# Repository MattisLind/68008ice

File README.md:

# RP2350 MC68008 Emulator and Bus Analyzer

A compact diagnostic adapter for computers using the **48-pin MC68008**. An
RP2350B or RP2354B microcontroller will use PIO, DMA and native USB to observe
the processor bus, generate diagnostic bus cycles and eventually emulate the
CPU in software.

The project now has a [draft pin map, candidate BOM and single-A3 KiCad schematic](kicad/README.md),
using RP2354B with in-package flash and **8 MiB QSPI PSRAM**, plus an
[unrouted four-layer placement starter](docs/mechanical.md). It uses provisional
outward-bent DIP contact lands and an accessible end tab. Firmware bring-up
now includes a [Docker Pico SDK build and verified SWD debugger workflow](docs/bringup.md)
for the standalone Waveshare Core2350B: GPIO39 blink, USB logging, flash read-back,
breakpoints, stepping and halt/resume. Two Core2350B boards have also been
verified with concurrent, independent debugger sessions through one probe on
a shared multidrop SWD connection. A GPIO0 link through the user's 470 ohm
resistor was verified with opposite LED states. The current
[GPIO0–44 connectivity test](docs/gpio-connectivity.md) scans both directions
with LOW and HIGH patterns through SWD. **All 45 paths pass in both directions**
after the user reflowed GPIO6's solder joints on 2026-11-16. The earlier expanded
scans detected that missing path; the earlier GPIO0–38 test found GPIO2's solder
fault before repair. No missing paths, cross-wiring or bridges are detected in
the latest scan. A [PIO bench analyzer and pattern generator](docs/pio-trace.md)
now capture GPIO0–31 and GPIO32–44 in separate 1024-sample runs at a nominal
150 MS/s. Both banks matched the one-bit-per-clock pattern with no receiver
FIFO stalls. The receiver stores `LOW32.VCD` and `HIGH13.VCD` in flash and
exports a read-only USB drive after acquisition; both files survived an SWD reset.
The current [core 0 dispatcher](docs/dispatcher.md) loads generator/analyzer
modules from flash or PSRAM into core 1 execution SRAM. A framed USB CDC
protocol and Python CLI start both applications without SWD. The analyzer
supports HIGH/LOW level triggers on any GPIO0–44 for either bank in its original
finite burst mode.
The dispatcher now exposes only USB CDC; the `ICECAP` mass-storage interface
has been removed. Captures remain in flash and download through CDC.
Dispatcher 0.3 adds an [8 MHz-timed 68008 bench bus generator, a 1 KiB memory
responder and state analyzer](docs/bus-fixture.md). Continuous timing and state
captures support 1..65536 records, address or GPIO triggers, early/middle/late
positions, partial stops and host VCD export. Continuous timing currently accepts
1 kHz..1 MHz; the original finite 150 MS/s path remains available. These are
3.3 V fixture applications with GPIO31 as DTACK, separate from the proposed
motherboard adapter. Dispatcher 0.4 adds a [combined memory/150 MS/s timing
mode](docs/single-cycle-timing.md) for a 4096-sample single-cycle trace with
an exact sampled-edge midpoint trigger. The 100 ms no-trigger capture/timeout
path and single read/write captures are bench verified on both boards, with
zero sampling stalls. The responder currently adds one or two wait states;
the nominal 500 ns no-wait cycle remains a sequencing target. Adapter bus
firmware remains unimplemented. Dispatcher 0.5 adds a
[CPU reset/STOP application](docs/cpu-emulator.md) using the shared PIO byte
bus engine and a boot image in the other board's memory/state analyzer. Both
boards passed reset-vector fetches and `STOP #$2700` (12 captured byte reads),
NOP/STOP (14 reads), and a separate reset-vector BERR-to-HALT test. This is a
reset/NOP/STOP milestone. Dispatcher 0.6 now runs the first five instructions
of the [supplied ABC1600 ROM](docs/abc1600.md), uploaded through the memory
tool into a separate 1 MiB target map. Both cause-register branch paths match
the captured bus bytes and per-instruction register snapshots. CLR,
MOVE/MOVEA, BTST, BRA/BSR/Bcc and JMP passed 37586 independent Musashi
comparisons in host RAM, including the legal MOVE addressing-mode cross-product.
Dispatcher 0.7 now separates generic uploaded-code memory from an ABC1600
memory application with boot-ROM mirrors, task/segment/page registers, MMU
translation and protection. The ROM executes **105 instructions** (the first
five plus the next 100), including 54 MAC writes; all 354 bus transfers, 106
CPU snapshots and MAC tables match the host/MAME reference. The expanded
CPU core passes 81238 independent instruction cases, and the MAC model passes
17133 comparisons against methods extracted from the local MAME checkout.
The extended interpreter now boots the ROM to its **keyboard input wait**
(host: 552468 instructions). A two-board run of 600000 instructions matched
all final registers and 4096 captured bus transfers, with zero bus errors.
See [keyboard boot validation](docs/validation/abc1600-keyboard-2026-11-17/README.md).
The instruction matrix passes 87274 Musashi comparisons. Functional CIO,
DART, SCC, CRTC, VRAM and mover support covers this boot path; complete
peripherals, exception processing, interrupts, remaining opcodes and
CPU-speed validation remain future work. The
[RP2350 engineering specification](requirements/RP2350_68008_ICE_Specification_and_Codex_Prompt.md)
is the design baseline and contains the detailed requirements, acceptance
criteria and primary references.

## Operating modes

| Mode | Physical CPU | Intended behavior |
| --- | --- | --- |
| Passive analyzer | Installed in the upper socket | CPU pins connect directly to the motherboard; the MCU observes with all bus outputs disabled. Capture bounded traces with triggers, timestamps and overflow reporting. |
| CPU replacement | Removed | The MCU drives the motherboard bus. Begin with byte reads/writes and memory diagnostics, then add a software MC68008 interpreter and execution controls. |

Passive mode is the default. A hardware interlock must prevent accidental MCU
bus driving with a real processor installed. Full CPU emulation and original
CPU-speed performance remain development goals requiring validation.

## Hardware concept

- Aligned female contacts on top and male contacts underneath: 48-pin DIP,
  2.54 mm contact pitch and 15.24 mm row spacing, with verified pin-for-pin
  correspondence in the schematic. The PCB has co-registered outward-facing
  SMT lands for manually formed tails; physical connector fit is provisional.
- A central 10 × 10 mm QFN-80 RP2350B/RP2354B, targeting a board close to the DIP
  body footprint. Connector geometry, component clearance and insertion forces
  must be checked before committing to the arrangement.
- Four-layer PCB: top signals, GND plane, 3.3 V plane and bottom signals.
  The placement starter is 70.96 mm long, with a 21 mm-wide CPU section and a
  27 mm-wide tab for USB/SWD/buttons/mode bridge. The electronic-component
  BOM target is under US$10, excluding PCB, connectors, assembly and freight;
  this is an unverified target.
- Native USB-C for host communication, BOOTSEL recovery and dedicated SWD for
  MCU debugging. RP2354B is the draft choice to save external-flash space;
  RP2350B with external QSPI flash remains an alternative.
- Raspberry Pi Debug Probe for SWD uploads and debugging, through J4's keyed
  3-pin JST-SH connector (C160403), using the probe's supplied cable. The ICE
  takes no power through this connector. See the [programming guide](docs/programming.md).
- U5 **APS6404L-3SQR-ZR / C3040877** adds 8 MiB PSRAM on the shared QSPI
  clock/data lines, with GPIO47 as its separate chip select. USB presence moves
  to GPIO46; the unused BUS_ARM_REQUEST reservation is removed.
- Target-derived 5 V supplies a 3.3 V regulator and the MCU's core-regulator
  circuit. The USB-C starter uses VBUS only for MOSFET-isolated presence sensing.
  Protection of direct bus GPIOs during supply transitions remains unresolved.
- The [per-pin allocation](kicad/mc68008_pinmap.csv) uses 40 five-volt-tolerant
  GPIOs and five 2.2 kΩ/BAT54-protected inputs, keeping address/data/strobes/clock in one PIO
  window. Cross-PIO timing and electrical acceptance still require validation.

RESET/HALT behavior, bus arbitration, TTL compatibility and supply sequencing
are explicit design checks. Connector footprints and the proposed input clamps
are provisional until verified against original documentation and bench tests.

## Development order

1. **Mechanical feasibility:** create a placement-first KiCad project with
   aligned top/bottom contacts, board outline, central MCU and provisional
   support components. Produce placement plots, a dimensions report and
   connector/clearance findings before detailed routing.
2. **Circuit design and bring-up:** complete the schematic, reviewed pin map,
   power/protection and hardware mode interlock. Bring up safe GPIO defaults,
   USB, recovery and target-clock observation.
3. **Passive analyzer:** implement synchronized PIO/DMA capture, bounded buffers,
   triggers and USB trace export to text/CSV. Verify that pass-through operation
   leaves a known-good target unaffected.
4. **Active diagnostics:** with the real CPU removed, validate byte transactions,
   timeouts, bus errors and ordered word/long accesses using a bench fixture.
   Add memory examination and explicitly enabled RAM writes/tests.
5. **CPU emulation:** evaluate MCL68+ licensing and portability, isolate the
   interpreter from the hardware bus engine, and test 68008 addressing,
   exceptions and interrupts. Benchmark before making speed claims.

The first firmware target uses Pico C/C++ SDK 2.3.1. Run `make setup`,
`make program`, and `make debug-check` for standalone Core2350B bring-up;
`make debug` opens interactive GDB inside Docker. On macOS, native OpenOCD
bridges the USB probe to container GDB. The dispatcher provides loadable bench
bus/analyzer modules and a versioned USB command protocol. The motherboard
adapter and full instruction interpreter remain planned; the bench interpreter
executes the ABC1600 ROM through its keyboard input wait on the two-board fixture.

For the configured two-board bench setup, `make multidrop-probe` enumerates both
chips and `make multidrop-check` tests two concurrent GDB sessions, independent
halt/resume, breakpoints, stepping and variable writes. The
[multidrop instructions](docs/bringup.md#two-boards-on-one-swd-probe-2026-11-15)
describe firmware IDs, USB recovery and interactive debugging.
The current boards run the [USB dispatcher](docs/dispatcher.md).
`make dispatcher-build` builds both images and separate loadable modules.
`python3 tools/ice.py fixture --generator /dev/cu.usbmodem24401 --receiver /dev/cu.usbmodem24301`
starts both applications and downloads verified VCD/raw captures. The Python
CLI also exposes load, upload, capture, generate, status, stop and fetch commands;
use `FIRMWARE=dispatcher` for interactive debugging.
The earlier [PIO trace fixture](docs/pio-trace.md) and its
`make pio-trace-capture` SWD workflow require their matching images to be reloaded.
The earlier [GPIO connectivity fixture](docs/gpio-connectivity.md) remains available:
`make gpio-connectivity-build` builds both images; `make gpio-connectivity-check`
reports opens, wrong pins and other observed faults. Use
`FIRMWARE=gpio_connectivity` for interactive debugging of these images. All
test pins are inputs between checks; the earlier GPIO0/LED demo remains a
separate `gpio_link` target.

The [JLCPCB upload BOM](kicad/BOM_JLCPCB.csv) uses dated C-number selections,
preferring Basic SMT parts and sharing values. The DIP contacts are fitted manually.
The prototype assumes shared target-only power and a TTL-compatible bus; its
BAT54 forward-voltage margin is accepted, with [nominal SPICE evidence](simulations/bat54/README.md).
Local supply transitions and input timing still need validation.

The next hardware milestone is **physical connector fit and placement review**,
then routing, alongside resolving independent output inhibition. The mode
jumper currently provides firmware permission only. No PCB is ready for fabrication.

## Repository

- [requirements/RP2350_68008_ICE_Specification_and_Codex_Prompt.md](requirements/RP2350_68008_ICE_Specification_and_Codex_Prompt.md): current engineering specification and staged implementation prompt.
- [docs/hardware.md](docs/hardware.md): pin-map rationale, PIO constraints, BOM decisions and open items.
- [docs/mechanical.md](docs/mechanical.md): provisional contact footprints, board dimensions, layer stack, placement plots and remaining fit/DRC checks.
- [docs/programming.md](docs/programming.md): SWD wiring, automated firmware uploads and debugging workflow.
- [docs/bringup.md](docs/bringup.md): Docker setup, Core2350B blink/debug commands and measured bring-up results.
- [docs/gpio-connectivity.md](docs/gpio-connectivity.md): GPIO0–44 wiring scan, debugger protocol and measured pin report.
- [docs/pio-trace.md](docs/pio-trace.md): two-bank PIO generator/analyzer, flash-backed USB VCD retrieval and measured results.
- [docs/dispatcher.md](docs/dispatcher.md): core 0 USB dispatcher, core 1 application loading, Python command interface and hardware acceptance results.
- [docs/protocol-v1.md](docs/protocol-v1.md): versioned CDC framing, CRC/replay rules, command table and status records.
- [firmware/](firmware/): standalone Core2350B fixtures, dispatcher, loadable applications and board configuration.
- [docker/Dockerfile](docker/Dockerfile): Pico SDK, Arm compiler, GDB, picotool and RP2350 OpenOCD.
- [kicad/README.md](kicad/README.md): editable schematic, PDF, pin tables, BOM and validation commands.
- [tools/](tools/): reproducible schematic generation and netlist/BOM checks.
- [AGENTS.md](AGENTS.md): project-specific instructions for contributors and coding agents.
- [LICENSE](LICENSE): Apache License 2.0.

## Version control

Keep the requirements, documentation, tools, circuit definitions, native KiCad
schematic/project/PCB, custom design rules, project libraries, library tables, pin
maps and component catalog in Git. The saved schematic includes manual layout
edits and must be preserved even though a generator also exists.

Keep the BOMs, selected schematic/placement PDFs, placement SVG and validation summary as review
deliverables. Keep the BAT54 model, simulation inputs and the documented result
snapshot under `simulations/bat54/`, including its provenance and log. These
selected outputs support review without requiring every reader to run the tools.

Everything under `build/`, including `build/hardware/`, is disposable working
output: netlists, ERC reports, preview images, backup snapshots and temporary
scripts. It is ignored. Reusable tools belong in `tools/`; results worth retaining
belong in a documented evidence directory or the validation summary. KiCad's
personal `.kicad_prl` file, locks, automatic backups and footprint-info cache are
also ignored, together with Python caches/local environments and OS metadata.

`kicad/parts_catalog.json` is a curated, dated selection record rather than a live
inventory cache. Version it alongside the matching schematic and BOM. Recheck
stock, prices and Basic/Extended status before ordering. Refresh the recorded
fields deliberately when they change, keeping part identity, footprint, source,
verification date and selection reasons consistent across purchasing outputs
and schematic fields. A checkout or build should not automatically replace
these reviewed selections with whatever the supplier currently lists.

The ABC1600 memory-controller port retains MAME's per-file BSD-3-Clause/Curt
Coder attribution; see [its license](LICENSES/BSD-3-Clause-MAME.txt).

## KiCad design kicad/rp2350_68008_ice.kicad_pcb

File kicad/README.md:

# RP2354B / MC68008 schematic starter

Open [rp2350_68008_ice.kicad_pro](rp2350_68008_ice.kicad_pro) in **KiCad 10**,
then its schematic. Everything is on **one landscape A3 sheet**, with local
signal labels and real power symbols. The
[single-page PDF](rp2350_68008_ice.pdf) is a review export.

| Area | Contents |
| --- | --- |
| Upper left | Pin-for-pin top socket / motherboard plug, sharing C23 bypass |
| Upper centre | RP2354B, clock/recovery, SWD, five BAT54 clamps and mode permission |
| Upper right | U5 8 MiB PSRAM, R4 chip-select pull-up and C24/C25 decoupling |
| Lower left | Supplies, MCU decoupling and rail load |
| Lower centre | USB-C, VBUS detector and data protection |

The [hardware review](../docs/hardware.md) explains mapping, component choices,
PIO constraints, budget and unresolved electrical/mechanical work. Read it before
using [BOM.csv](BOM.csv) for procurement. The
[native PCB](rp2350_68008_ice.kicad_pcb) now contains all 63 footprints and an
unrouted four-layer placement study. J1/J2 use provisional outward-bent SMT
contact lands, and JP1 has an open solder-bridge footprint.
J4 is a purchased JST-SH connector for button-free firmware uploads and debugging
with the Raspberry Pi Debug Probe. The [programming guide](../docs/programming.md)
describes probe wiring and automation.

The [mechanical notes](../docs/mechanical.md) describe the **70.96 mm length,
21 mm CPU section, 27 mm end tab** and the top/GND/3V3/bottom layer stack.
[placement.pdf](placement.pdf) shows top and bottom views. USB, SWD, BOOTSEL,
RUN and the mode bridge occupy the accessible end. The contact pads coincide
in X/Y on opposite faces, with bottom-side numbering checked independently.
Their bent-lead dimensions and socket/adapter heights need a physical fit check.

## Mapping and regeneration

- [mc68008_pinmap.csv](mc68008_pinmap.csv): all 48 DIP pins and their MCU paths.
- [rp2354b_gpio.csv](rp2354b_gpio.csv): all 48 GPIOs, including mode, USB sense and PSRAM select.
- [rp2350_ice.kicad_sym](rp2350_ice.kicad_sym): project symbols; RP2354B uses the
  documented RP2350B-compatible pinout, and socket symbols have passive pins.
- [rp2350_ice.pretty](rp2350_ice.pretty): reference-derived
  core-inductor footprint (license in `reference/`), two provisional DIP48
  formed-tail footprints and a hand-solder bridge.
- [BOM.csv](BOM.csv): engineering BOM with C-numbers, Basic/Extended class,
  assembly method and selection evidence.
- [BOM_JLCPCB.csv](BOM_JLCPCB.csv): grouped JLCPCB upload BOM, including J4 and
  excluding J1/J2 manual contacts and the JP1 PCB solder bridge.
- [parts_catalog.json](parts_catalog.json) and [JLCPCB_parts.md](JLCPCB_parts.md):
  dated catalog selections and rationale for every Extended type.

The generated sheet is editable. Circuit definitions are in
[hardware_circuit.json](../tools/hardware_circuit.json); the generator holds the
placement table. Review/save any GUI changes before regeneration, which replaces
the drawing. From the repository root:

```sh
python3 tools/build_hardware.py --overwrite
```

The generator uses Python's standard library and installed KiCad 10 symbols.
Set `KICAD_SYMBOL_DIR` if they are outside the detected platform directories.
Keep mapping, catalog, generator, generated schematic and BOM changes together.

The saved drawing includes manual layout improvements. To update BOMs and the
GPIO table without replacing that drawing, use:

```sh
python3 tools/build_hardware.py --bom-only
```

The five single **R+O BAT54X / C19627026** clamps use SOD-523 footprints and plain
two-pin Schottky symbols beside the MCU. Pad 1 is cathode, pad 2 is anode;
the old SOT-23 symbol and NC terminal are removed. U5
**APS6404L-3SQR-ZR / C3040877** uses GPIO47 for QMI CS1 and
shares the dedicated QSPI clock/data pads with the 2 MB in-package flash.
USB_PRESENT_N moves to GPIO46 and BUS_ARM_REQUEST is removed. R4 is repurposed
as a 1 kΩ CS pull-up; R5 remains MODE_PERMIT's 10 kΩ pull-down. C24/C25 reuse
existing 4.7 µF / 100 nF parts. The rest of the saved layout is preserved.

J4 is **JST SM03B-SRSS-TB(LF)(SN) / C160403**, a side-entry, 3-pin, 1.0 mm
pitch SMT connector matching the Raspberry Pi Debug Probe's supplied cable.
Contacts are **1 SWCLK, 2 GND, 3 SWDIO**, with grounded mounting tabs and no
power/reference contact. Its standard KiCad footprint is assigned; plug access
and clearance from the CPU/socket remain placement checks.

The PSRAM uses KiCad's standard USON footprint with a 0.2 × 1.6 mm centre
paddle, left unconnected. Source, startup, power and timing details are in the
[PSRAM hardware notes](../docs/hardware.md#8-mib-psram). Firmware must select
GPIO47 explicitly; automatic CS discovery could drive target address lines.

## Checks and exports

With `kicad-cli` on PATH, from the repository root:

```sh
mkdir -p build/hardware
kicad-cli version
kicad-cli sch export netlist --format kicadxml \
  -o build/hardware/netlist.xml kicad/rp2350_68008_ice.kicad_sch
python3 tools/check_hardware.py build/hardware/netlist.xml
python3 tools/check_clamp_budget.py
kicad-cli sch erc --format json \
  -o build/hardware/erc.json kicad/rp2350_68008_ice.kicad_sch
kicad-cli sch export pdf \
  -o kicad/rp2350_68008_ice.pdf kicad/rp2350_68008_ice.kicad_sch
```

Validation with KiCad **10.0.5**: connectivity/BOM checks pass; ERC reports **zero
errors and zero warnings**. No ERC exclusions were added. The local inductor,
two-pad switch and three-pin JST-SH footprints were checked separately.
See [validation.md](validation.md). PCB correspondence and DIP pad alignment
checks pass; DRC reports four USB locating-hole clearances plus the expected
unrouted connections. Physical fit, shared-power transitions, interlock and PIO
timing remain open. The user accepts the BAT54 forward-voltage
margin, supported by the [nominal SPICE results](../simulations/bat54/README.md).

Run `tools/check_pcb.py` with a Python interpreter containing KiCad's `pcbnew`
module. The board generator `tools/start_pcb.py` refuses to replace an existing
board without `--overwrite`; use the saved native PCB for further GUI editing.

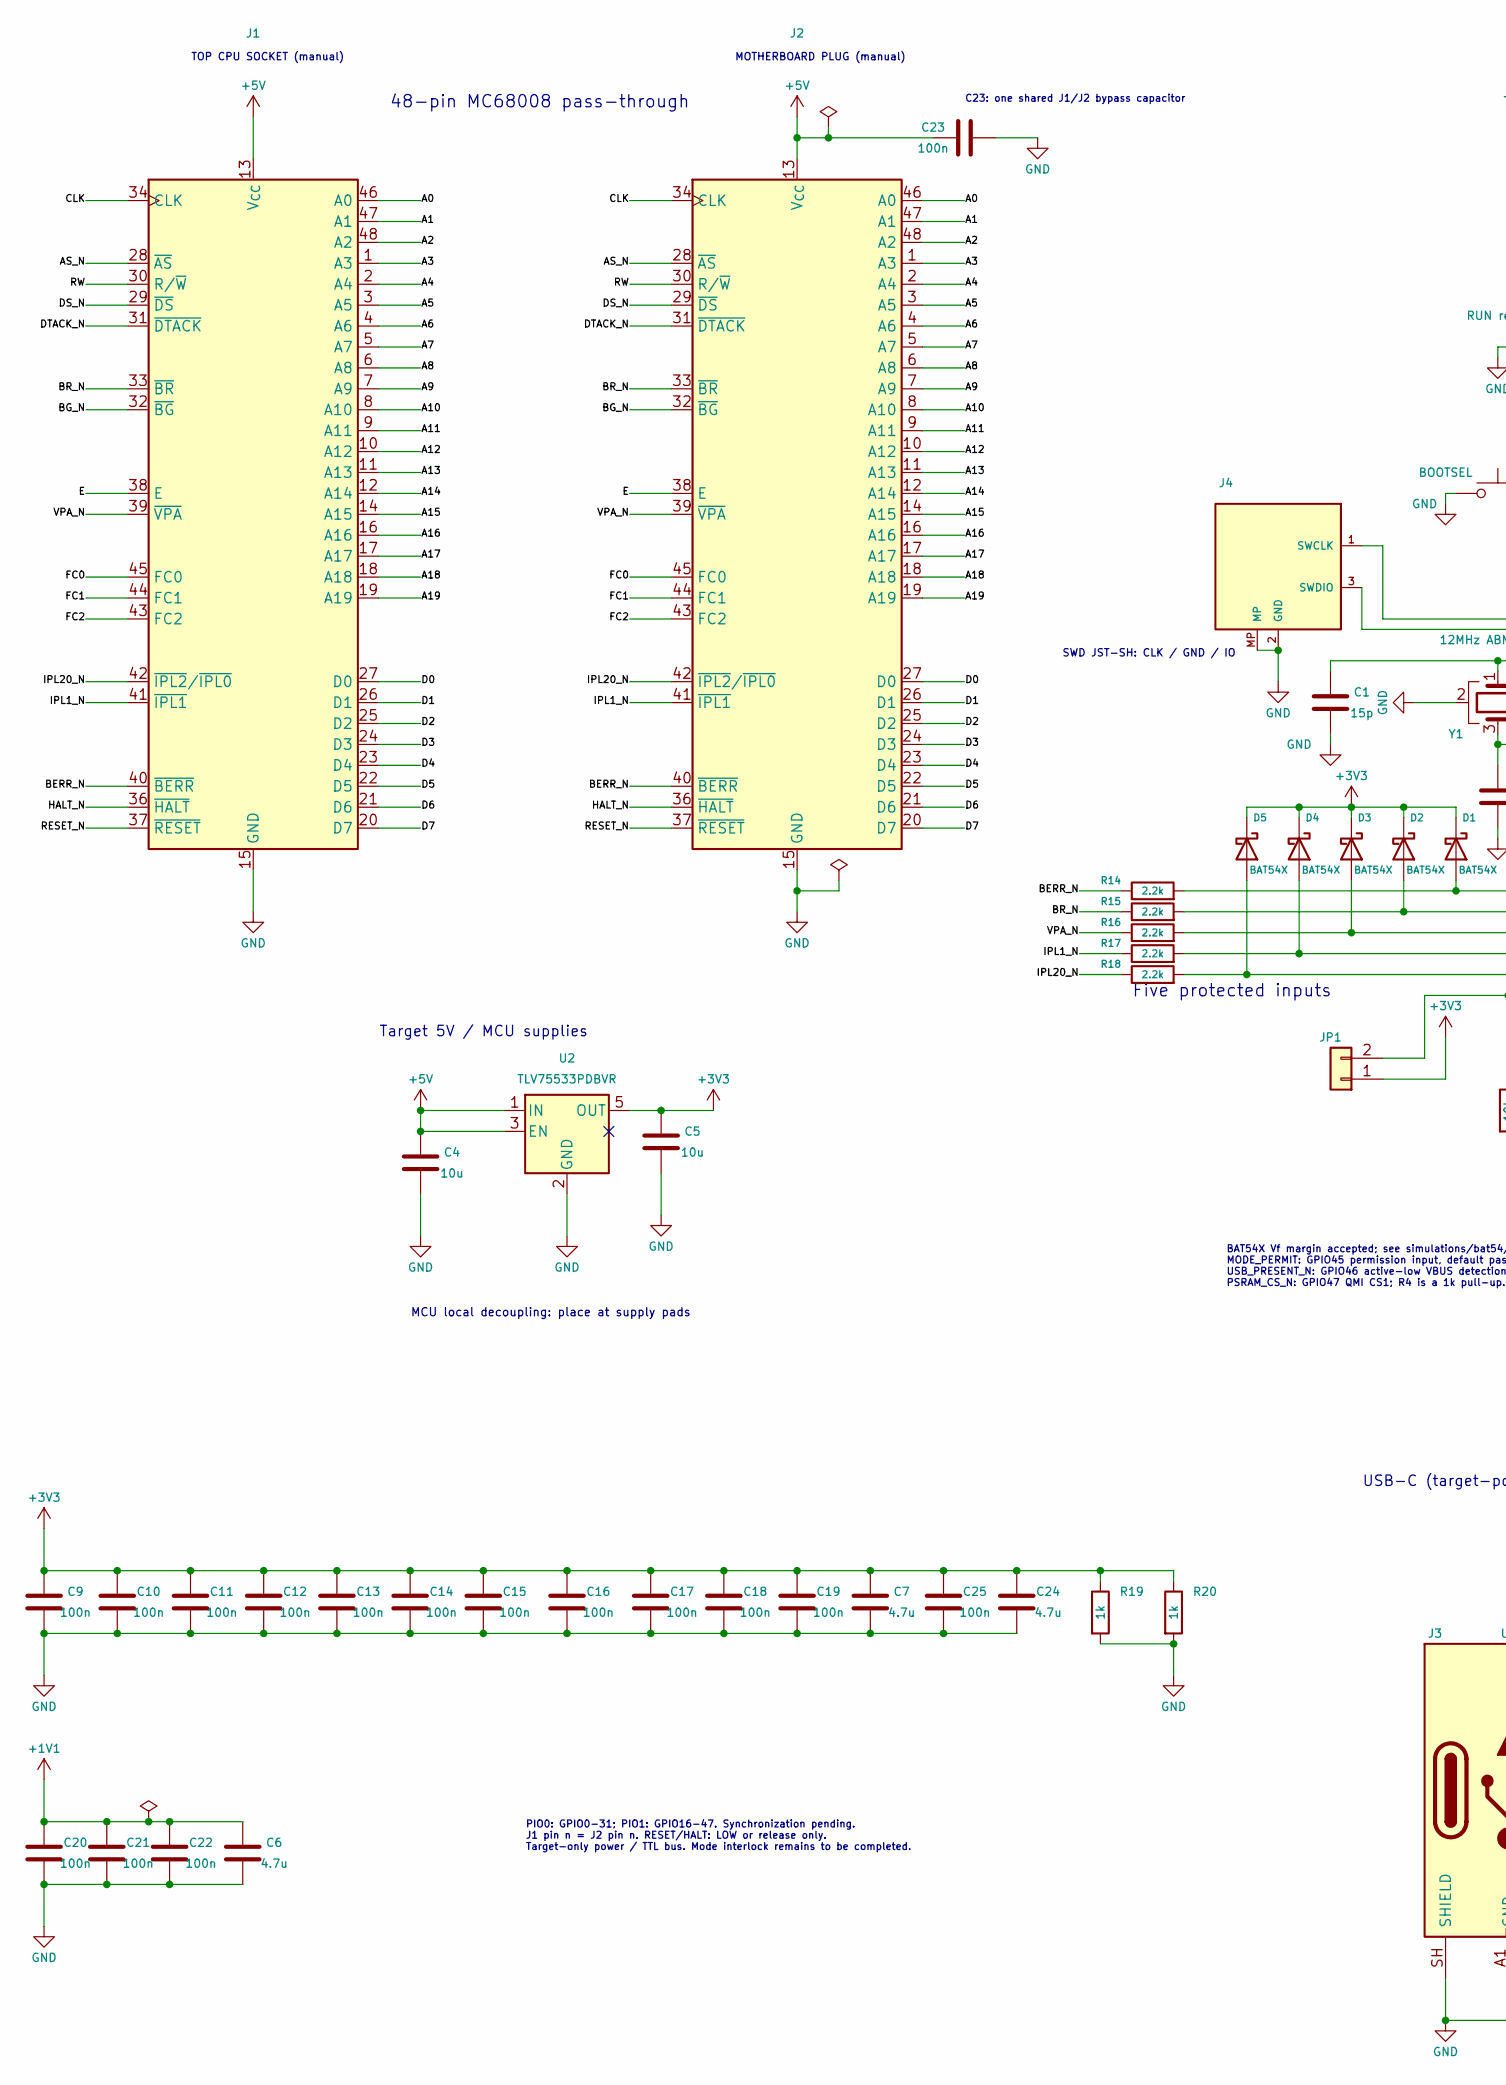
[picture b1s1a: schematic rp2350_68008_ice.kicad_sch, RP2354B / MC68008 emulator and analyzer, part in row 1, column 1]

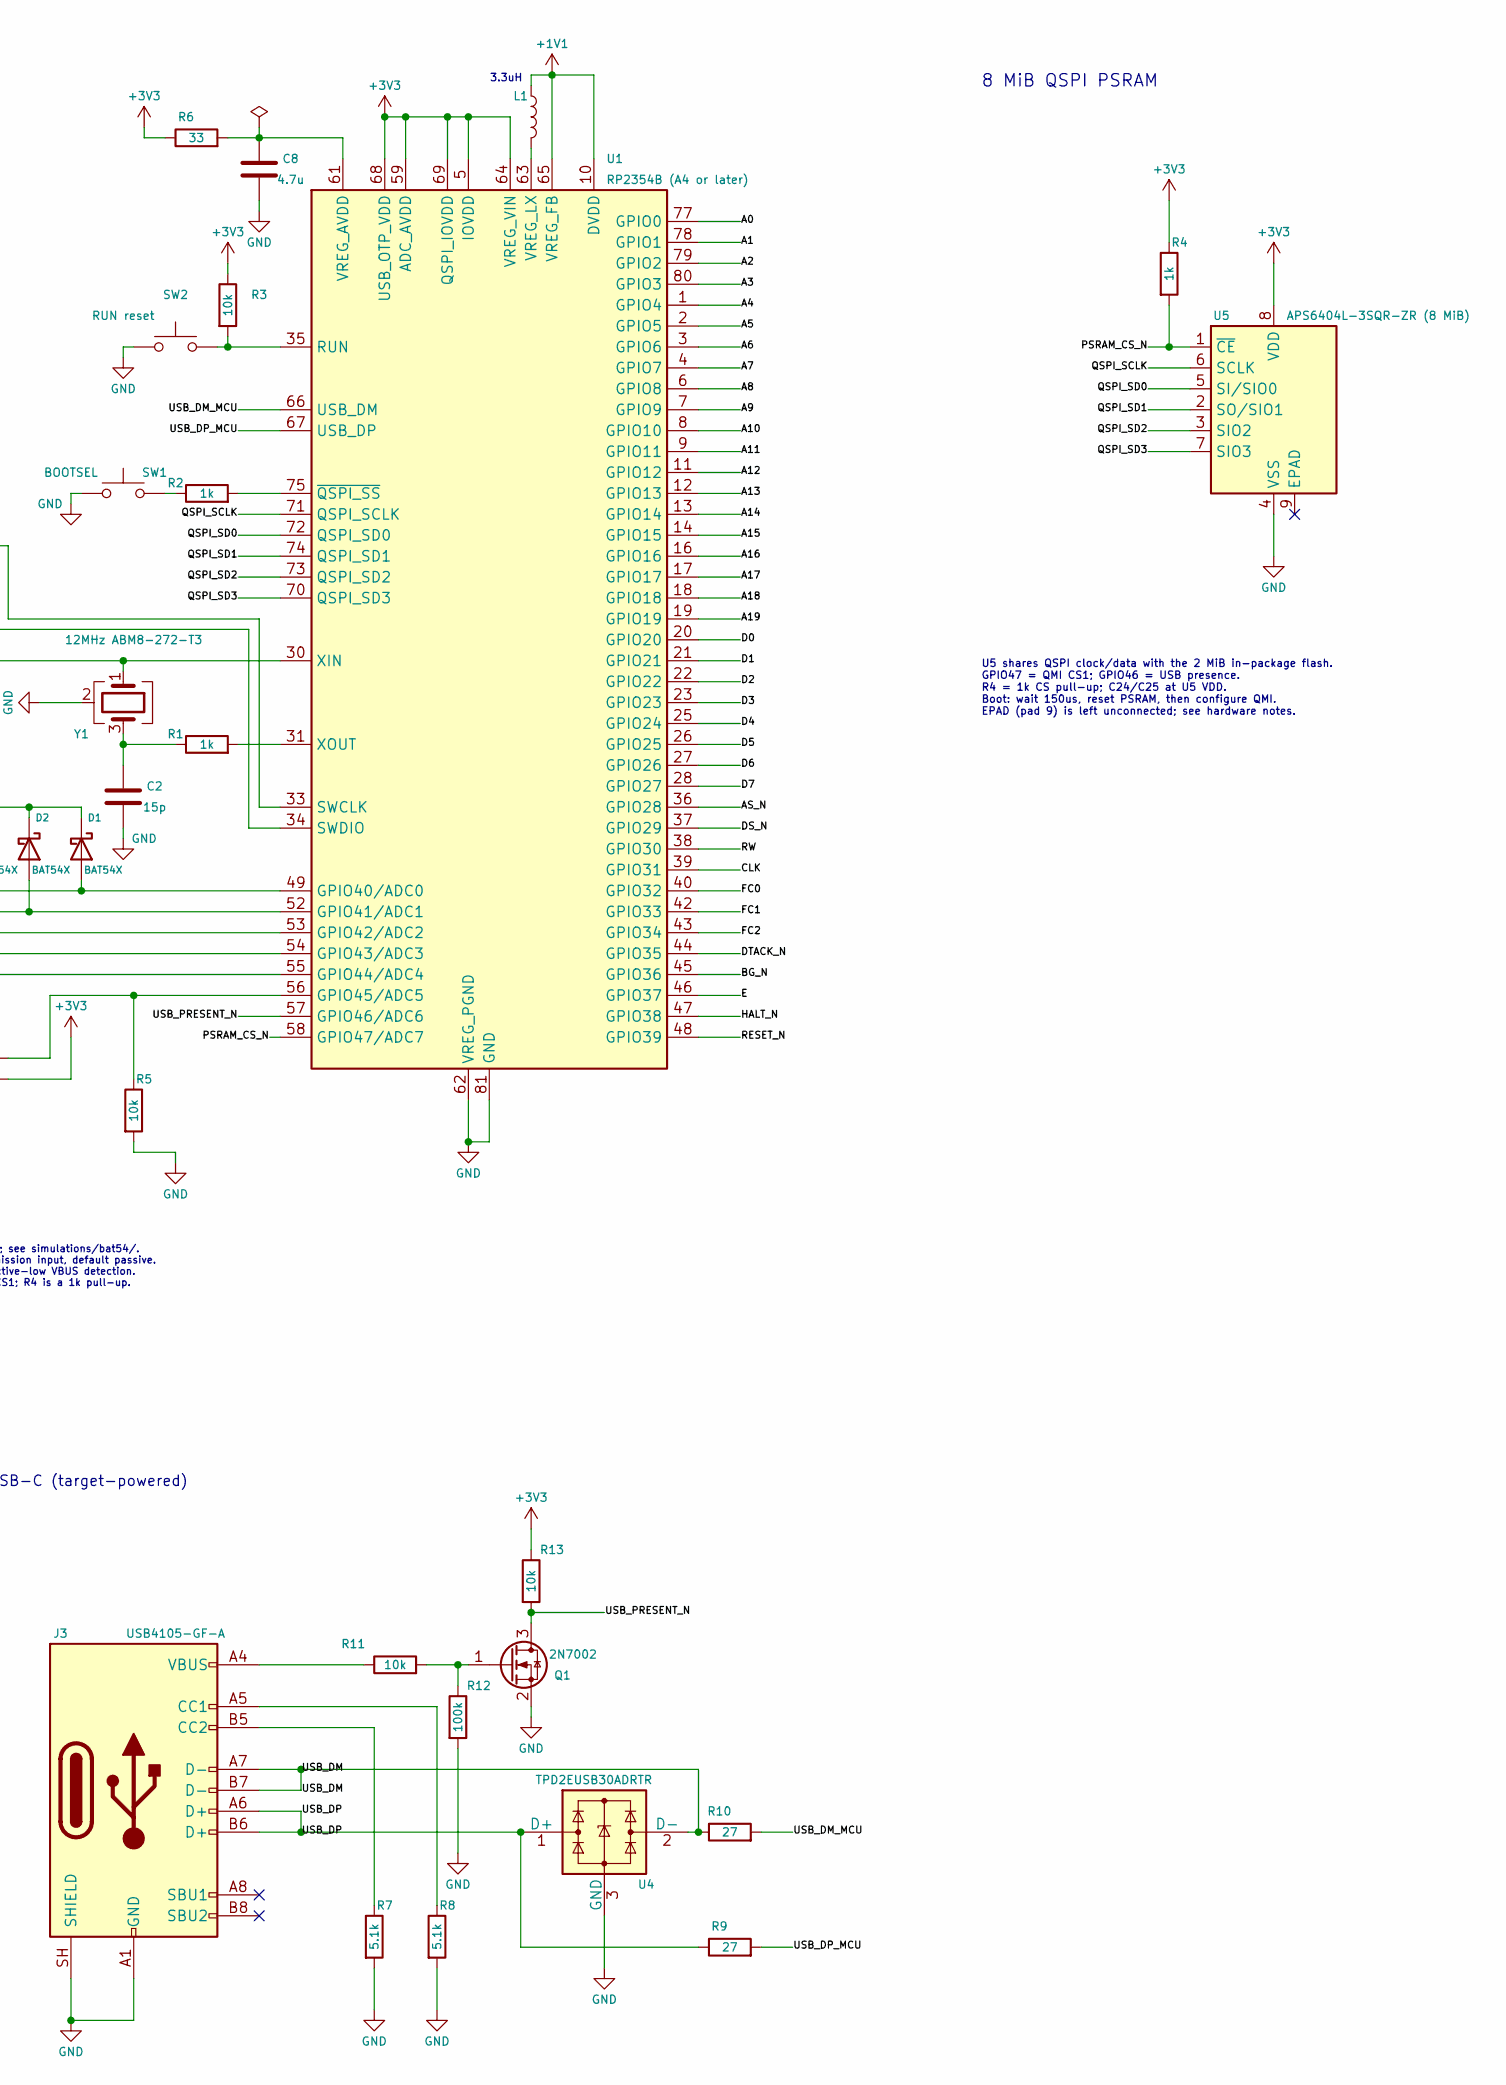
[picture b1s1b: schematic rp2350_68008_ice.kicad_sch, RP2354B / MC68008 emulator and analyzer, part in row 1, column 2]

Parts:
C1, C2: 15p; C_0402_1005Metric; MPN 0402CG150J500NT; LCSC C1548
C4, C5: 10u; C_0805_2012Metric; MPN CL21A106KAYNNNE; LCSC C15850
C6, C7, C8, C24: 4.7u; C_0402_1005Metric; MPN CL05A475MP5NRNC; LCSC C23733
C9, C10, C11, C12, C13, C14, C15, C16, C17, C18, C19, C20, C21, C22, C23, C25: 100n; C_0402_1005Metric; MPN CL05B104KO5NNNC; LCSC C1525
D1, D2, D3, D4, D5: BAT54X; D_SOD-523; MPN BAT54X; LCSC C19627026
J1: CPU TOP SOCKET - bent tails (provisional); DIP48_BentTail_Top; MPN TBD
J2: TARGET BOTTOM ADAPTER - bent tails (provisional); DIP48_BentTail_Bottom_Mirrored; MPN TBD
J3: USB4105-GF-A; USB_C_Receptacle_GCT_USB4105-xx-A_16P_TopMnt_Horizontal; MPN USB4105-GF-A; LCSC C3020560
J4: SWD JST-SH; JST_SH_SM03B-SRSS-TB_1x03-1MP_P1.00mm_Horizontal; MPN SM03B-SRSS-TB(LF)(SN); LCSC C160403
JP1: ACTIVE PERMIT - solder bridge open=PASSIVE; SolderBridge_2_Open_HandSolder; MPN PCB_FEATURE
L1: 3.3u AOTA-B201610S3R3-101-T; AOTA-B201610S3R3-101-T; MPN AOTA-B201610S3R3-101-T; LCSC C42411119
Q1: 2N7002; SOT-23; MPN 2N7002; LCSC C8545
R1, R2, R4, R19, R20: 1k; R_0402_1005Metric; MPN 0402WGF1001TCE; LCSC C11702
R3, R5, R11, R13: 10k; R_0402_1005Metric; MPN 0402WGF1002TCE; LCSC C25744
R6: 33; R_0402_1005Metric; MPN 0402WGF330JTCE; LCSC C25105
R7, R8: 5.1k; R_0402_1005Metric; MPN 0402WGF5101TCE; LCSC C25905
R9, R10: 27; R_0402_1005Metric; MPN 0402WGF270JTCE; LCSC C25100
R12: 100k; R_0402_1005Metric; MPN 0402WGF1003TCE; LCSC C25741
R14, R15, R16, R17, R18: 2.2k; R_0402_1005Metric; MPN 0402WGF2201TCE; LCSC C25879
SW1: BOOTSEL; SW_SPST_TS-1088-xR020; MPN TS-1088-AR02016; LCSC C720477
SW2: RUN reset; SW_SPST_TS-1088-xR020; MPN TS-1088-AR02016; LCSC C720477
U1: RP2354B (A4 or later); QFN-80-1EP_10x10mm_P0.4mm_EP3.4x3.4mm; MPN RP2354B; LCSC C39843328
U2: TLV75533PDBVR; SOT-23-5; MPN TLV75533PDBVR; LCSC C404027
U4: TPD2EUSB30ADRTR; Texas_DRT-3; MPN TPD2EUSB30ADRTR; LCSC C94934
U5: APS6404L-3SQR-ZR (8 MiB); Winbond_USON-8-1EP_3x2mm_P0.5mm_EP0.2x1.6mm; MPN APS6404L-3SQR-ZR; LCSC C3040877
Y1: 12MHz ABM8-272-T3; Crystal_SMD_3225-4Pin_3.2x2.5mm; MPN ABM8-272-T3; LCSC C20625731

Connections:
+1V1: C6.1, C20.1, C21.1, C22.1, L1.1, U1.10 (DVDD), U1.32 (DVDD), U1.51 (DVDD), U1.65 (VREG_FB)
+3V3: C5.1, C7.1, C9.1, C10.1, C11.1, C12.1, C13.1, C14.1, C15.1, C16.1, C17.1, C18.1, C19.1, C24.1, C25.1, D1.1 (K), D2.1 (K), D3.1 (K), D4.1 (K), D5.1 (K), JP1.1, R3.1, R4.1, R6.1, R13.1, R19.1, R20.1, U1.5 (IOVDD), U1.15 (IOVDD), U1.24 (IOVDD), U1.29 (IOVDD), U1.41 (IOVDD), U1.50 (IOVDD), U1.59 (ADC_AVDD), U1.60 (IOVDD), U1.64 (VREG_VIN), U1.68 (USB_OTP_VDD), U1.69 (QSPI_IOVDD), U1.76 (IOVDD), U2.5 (OUT), U5.8 (VDD)
+5V: C4.1, C23.1, J1.13 (V_{CC}), J2.13 (V_{CC}), U2.1 (IN), U2.3 (EN)
/A0: J1.46 (A0), J2.46 (A0), U1.77 (GPIO0)
/A1: J1.47 (A1), J2.47 (A1), U1.78 (GPIO1)
/A2: J1.48 (A2), J2.48 (A2), U1.79 (GPIO2)
/A3: J1.1 (A3), J2.1 (A3), U1.80 (GPIO3)
/A4: J1.2 (A4), J2.2 (A4), U1.1 (GPIO4)
/A5: J1.3 (A5), J2.3 (A5), U1.2 (GPIO5)
/A6: J1.4 (A6), J2.4 (A6), U1.3 (GPIO6)
/A7: J1.5 (A7), J2.5 (A7), U1.4 (GPIO7)
/A8: J1.6 (A8), J2.6 (A8), U1.6 (GPIO8)
/A9: J1.7 (A9), J2.7 (A9), U1.7 (GPIO9)
/A10: J1.8 (A10), J2.8 (A10), U1.8 (GPIO10)
/A11: J1.9 (A11), J2.9 (A11), U1.9 (GPIO11)
/A12: J1.10 (A12), J2.10 (A12), U1.11 (GPIO12)
/A13: J1.11 (A13), J2.11 (A13), U1.12 (GPIO13)
/A14: J1.12 (A14), J2.12 (A14), U1.13 (GPIO14)
/A15: J1.14 (A15), J2.14 (A15), U1.14 (GPIO15)
/A16: J1.16 (A16), J2.16 (A16), U1.16 (GPIO16)
/A17: J1.17 (A17), J2.17 (A17), U1.17 (GPIO17)
/A18: J1.18 (A18), J2.18 (A18), U1.18 (GPIO18)
/A19: J1.19 (A19), J2.19 (A19), U1.19 (GPIO19)
/AS_N: J1.28 (~AS), J2.28 (~AS), U1.36 (GPIO28)
/BERR_N: J1.40 (~BERR), J2.40 (~BERR), R14.1
/BG_N: J1.32 (~BG), J2.32 (~BG), U1.45 (GPIO36)
/BR_N: J1.33 (~BR), J2.33 (~BR), R15.1
/CLK: J1.34 (CLK), J2.34 (CLK), U1.39 (GPIO31)
/D0: J1.27 (D0), J2.27 (D0), U1.20 (GPIO20)
/D1: J1.26 (D1), J2.26 (D1), U1.21 (GPIO21)
/D2: J1.25 (D2), J2.25 (D2), U1.22 (GPIO22)
/D3: J1.24 (D3), J2.24 (D3), U1.23 (GPIO23)
/D4: J1.23 (D4), J2.23 (D4), U1.25 (GPIO24)
/D5: J1.22 (D5), J2.22 (D5), U1.26 (GPIO25)
/D6: J1.21 (D6), J2.21 (D6), U1.27 (GPIO26)
/D7: J1.20 (D7), J2.20 (D7), U1.28 (GPIO27)
/DS_N: J1.29 (~DS), J2.29 (~DS), U1.37 (GPIO29)
/DTACK_N: J1.31 (~DTACK), J2.31 (~DTACK), U1.44 (GPIO35)
/E: J1.38 (E), J2.38 (E), U1.46 (GPIO37)
/FC0: J1.45 (FC0), J2.45 (FC0), U1.40 (GPIO32)
/FC1: J1.44 (FC1), J2.44 (FC1), U1.42 (GPIO33)
/FC2: J1.43 (FC2), J2.43 (FC2), U1.43 (GPIO34)
/HALT_N: J1.36 (~HALT), J2.36 (~HALT), U1.47 (GPIO38)
/IPL1_N: J1.41 (~IPL1), J2.41 (~IPL1), R17.1
/IPL20_N: J1.42 (~IPL2/~IPL0), J2.42 (~IPL2/~IPL0), R18.1
/PSRAM_CS_N: R4.2, U1.58 (GPIO47/ADC7), U5.1 (~CE)
/QSPI_SCLK: U1.71 (QSPI_SCLK), U5.6 (SCLK)
/QSPI_SD0: U1.72 (QSPI_SD0), U5.5 (SI/SIO0)
/QSPI_SD1: U1.74 (QSPI_SD1), U5.2 (SO/SIO1)
/QSPI_SD2: U1.73 (QSPI_SD2), U5.3 (SIO2)
/QSPI_SD3: U1.70 (QSPI_SD3), U5.7 (SIO3)
/RESET_N: J1.37 (~RESET), J2.37 (~RESET), U1.48 (GPIO39)
/RW: J1.30 (R/~W), J2.30 (R/~W), U1.38 (GPIO30)
/USB_DM: J3.A7 (D-), J3.B7 (D-), R10.1, U4.2 (D-)
/USB_DM_MCU: R10.2, U1.66 (USB_DM)
/USB_DP: J3.A6 (D+), J3.B6 (D+), R9.1, U4.1 (D+)
/USB_DP_MCU: R9.2, U1.67 (USB_DP)
/USB_PRESENT_N: Q1.3 (D), R13.2, U1.57 (GPIO46/ADC6)
/VPA_N: J1.39 (~VPA), J2.39 (~VPA), R16.1
GND: C1.2, C2.2, C4.2, C5.2, C6.2, C7.2, C8.2, C9.2, C10.2, C11.2, C12.2, C13.2, C14.2, C15.2, C16.2, C17.2, C18.2, C19.2, C20.2, C21.2, C22.2, C23.2, C24.2, C25.2, J1.15 (GND), J1.35 (GND), J2.15 (GND), J2.35 (GND), J3.A1 (GND), J3.A12 (GND), J3.B1 (GND), J3.B12 (GND), J3.SH (SHIELD), J4.2 (GND), J4.MP, Q1.2 (S), R5.2, R7.2, R8.2, R12.2, R19.2, R20.2, SW1.1, SW2.1, U1.62 (VREG_PGND), U1.81 (GND), U2.2 (GND), U4.3 (GND), U5.4 (VSS), Y1.2 (G), Y1.4 (G)
unnamed: C2.1, R1.1, Y1.3
unnamed: D1.2 (A), R14.2, U1.49 (GPIO40/ADC0)
unnamed: D2.2 (A), R15.2, U1.52 (GPIO41/ADC1)
unnamed: D3.2 (A), R16.2, U1.53 (GPIO42/ADC2)
unnamed: D4.2 (A), R17.2, U1.54 (GPIO43/ADC3)
unnamed: D5.2 (A), R18.2, U1.55 (GPIO44/ADC4)
unnamed: J3.A5 (CC1), R8.1
unnamed: J3.B5 (CC2), R7.1
unnamed: J3.A4 (VBUS), J3.A9 (VBUS), J3.B4 (VBUS), J3.B9 (VBUS), R11.1
unnamed: J4.1 (SWCLK), U1.33 (SWCLK)
unnamed: J4.3 (SWDIO), U1.34 (SWDIO)
unnamed: JP1.2, R5.1, U1.56 (GPIO45/ADC5)
unnamed: Q1.1 (G), R11.2, R12.1
unnamed: R2.1, SW1.2
unnamed: R3.2, SW2.2, U1.35 (RUN)
unnamed: C8.1, R6.2, U1.61 (VREG_AVDD)
unnamed: L1.2, U1.63 (VREG_LX)
unnamed: C1.1, U1.30 (XIN), Y1.1
unnamed: R1.2, U1.31 (XOUT)
unnamed: R2.2, U1.75 (~QSPI_SS)

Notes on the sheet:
PIO0: GPIO0-31; PIO1: GPIO16-47. Synchronization pending. J1 pin n = J2 pin n. RESET/HALT: LOW or release only. Target-only power / TTL bus. Mode interlock remains to be completed.
U5 shares QSPI clock/data with the 2 MiB in-package flash. GPIO47 = QMI CS1; GPIO46 = USB presence. R4 = 1k CS pull-up; C24/C25 at U5 VDD. Boot: wait 150us, reset PSRAM, then configure QMI. EPAD (pad 9) is left unconnected; see hardware notes.
BAT54X Vf margin accepted; see simulations/bat54/. MODE_PERMIT: GPIO45 permission input, default passive. USB_PRESENT_N: GPIO46 active-low VBUS detection. PSRAM_CS_N: GPIO47 QMI CS1; R4 is a 1k pull-up.
MCU local decoupling: place at supply pads
USB-C (target-powered)
48-pin MC68008 pass-through
SWD JST-SH: CLK / GND / IO
TOP CPU SOCKET (manual)
Target 5V / MCU supplies
3.3uH
Five protected inputs
MOTHERBOARD PLUG (manual)
C23: one shared J1/J2 bypass capacitor
8 MiB QSPI PSRAM

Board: 4 copper layers, 63 parts (15 on the bottom side), 80 nets, no tracks yet.

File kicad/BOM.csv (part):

Reference,Quantity,Value,Footprint,Manufacturer,MPN,LCSC,JLCPCB_library,Assembly,JLCPCB_URL,Verified_date,Selection_reason,Source,Status
C1,1,15p,Capacitor_SMD:C_0402_1005Metric,FH (Guangdong Fenghua Advanced Tech),0402CG150J500NT,C1548,Basic,JLCPCB_SMT,https://jlcpcb.com/partdetail/0402CG150J500NT/C1548,2026-11-09,Basic C0G crystal load capacitors; both use the same part.,https://www.lcsc.com/datasheet/C1548.pdf,candidate
C2,1,15p,Capacitor_SMD:C_0402_1005Metric,FH (Guangdong Fenghua Advanced Tech),0402CG150J500NT,C1548,Basic,JLCPCB_SMT,https://jlcpcb.com/partdetail/0402CG150J500NT/C1548,2026-11-09,Basic C0G crystal load capacitors; both use the same part.,https://www.lcsc.com/datasheet/C1548.pdf,candidate
C4,1,10u,Capacitor_SMD:C_0805_2012Metric,Samsu,CL21A106KAYNNNE,C15850,Basic,JLCPCB_SMT,https://jlcpcb.com/partdetail/CL21A106KAYNNNE/C15850,2026-11-09,Basic 25V X5R for LDO input/output; same exact part.,https://www.lcsc.com/datasheet/C15850.pdf,candidate
C5,1,10u,Capacitor_SMD:C_0805_2012Metric,Samsu,CL21A106KAYNNNE,C15850,Basic,JLCPCB_SMT,https://jlcpcb.com/partdetail/CL21A106KAYNNNE/C15850,2026-11-09,Basic 25V X5R for LDO input/output; same exact part.,https://www.lcsc.com/datasheet/C15850.pdf,candidate
C6,1,4.7u,Capacitor_SMD:C_0402_1005Metric,Samsung Electro-Mechanics,CL05A475MP5NRNC,C23733,Basic,JLCPCB_SMT,https://jlcpcb.com/partdetail/CL05A475MP5NRNC/C23733,2026-11-09,"Basic 10V X5R; share core/filter and PSRAM local bypass value; verify effective capacitance, including at least 1uF at PSRAM VDD.",https://www.lcsc.com/datasheet/C23733.pdf,candidate
C7,1,4.7u,Capacitor_SMD:C_0402_1005Metric,Samsung Electro-Mechanics,CL05A475MP5NRNC,C23733,Basic,JLCPCB_SMT,https://jlcpcb.com/partdetail/CL05A475MP5NRNC/C23733,2026-11-09,"Basic 10V X5R; share core/filter and PSRAM local bypass value; verify effective capacitance, including at least 1uF at PSRAM VDD.",https://www.lcsc.com/datasheet/C23733.pdf,candidate
C8,1,4.7u,Capacitor_SMD:C_0402_1005Metric,Samsung Electro-Mechanics,CL05A475MP5NRNC,C23733,Basic,JLCPCB_SMT,https://jlcpcb.com/partdetail/CL05A475MP5NRNC/C23733,2026-11-09,"Basic 10V X5R; share core/filter and PSRAM local bypass value; verify effective capacitance, including at least 1uF at PSRAM VDD.",https://www.lcsc.com/datasheet/C23733.pdf,candidate
C9,1,100n,Capacitor_SMD:C_0402_1005Metric,Samsung Electro-Mechanics,CL05B104KO5NNNC,C1525,Basic,JLCPCB_SMT,https://jlcpcb.com/partdetail/CL05B104KO5NNNC/C1525,2026-11-09,"Basic common MCU, PSRAM and connector high-frequency bypass part.",https://www.lcsc.com/datasheet/C1525.pdf,candidate
C10,1,100n,Capacitor_SMD:C_0402_1005Metric,Samsung Electro-Mechanics,CL05B104KO5NNNC,C1525,Basic,JLCPCB_SMT,https://jlcpcb.com/partdetail/CL05B104KO5NNNC/C1525,2026-11-09,"Basic common MCU, PSRAM and connector high-frequency bypass part.",https://www.lcsc.com/datasheet/C1525.pdf,candidate
C11,1,100n,Capacitor_SMD:C_0402_1005Metric,Samsung Electro-Mechanics,CL05B104KO5NNNC,C1525,Basic,JLCPCB_SMT,https://jlcpcb.com/partdetail/CL05B104KO5NNNC/C1525,2026-11-09,"Basic common MCU, PSRAM and connector high-frequency bypass part.",https://www.lcsc.com/datasheet/C1525.pdf,candidate
C12,1,100n,Capacitor_SMD:C_0402_1005Metric,Samsung Electro-Mechanics,CL05B104KO5NNNC,C1525,Basic,JLCPCB_SMT,https://jlcpcb.com/partdetail/CL05B104KO5NNNC/C1525,2026-11-09,"Basic common MCU, PSRAM and connector high-frequency bypass part.",https://www.lcsc.com/datasheet/C1525.pdf,candidate
C13,1,100n,Capacitor_SMD:C_0402_1005Metric,Samsung Electro-Mechanics,CL05B104KO5NNNC,C1525,Basic,JLCPCB_SMT,https://jlcpcb.com/partdetail/CL05B104KO5NNNC/C1525,2026-11-09,"Basic common MCU, PSRAM and connector high-frequency bypass part.",https://www.lcsc.com/datasheet/C1525.pdf,candidate
C14,1,100n,Capacitor_SMD:C_0402_1005Metric,Samsung Electro-Mechanics,CL05B104KO5NNNC,C1525,Basic,JLCPCB_SMT,https://jlcpcb.com/partdetail/CL05B104KO5NNNC/C1525,2026-11-09,"Basic common MCU, PSRAM and connector high-frequency bypass part.",https://www.lcsc.com/datasheet/C1525.pdf,candidate
C15,1,100n,Capacitor_SMD:C_0402_1005Metric,Samsung Electro-Mechanics,CL05B104KO5NNNC,C1525,Basic,JLCPCB_SMT,https://jlcpcb.com/partdetail/CL05B104KO5NNNC/C1525,2026-11-09,"Basic common MCU, PSRAM and connector high-frequency bypass part.",https://www.lcsc.com/datasheet/C1525.pdf,candidate
C16,1,100n,Capacitor_SMD:C_0402_1005Metric,Samsung Electro-Mechanics,CL05B104KO5NNNC,C1525,Basic,JLCPCB_SMT,https://jlcpcb.com/partdetail/CL05B104KO5NNNC/C1525,2026-11-09,"Basic common MCU, PSRAM and connector high-frequency bypass part.",https://www.lcsc.com/datasheet/C1525.pdf,candidate
C17,1,100n,Capacitor_SMD:C_0402_1005Metric,Samsung Electro-Mechanics,CL05B104KO5NNNC,C1525,Basic,JLCPCB_SMT,https://jlcpcb.com/partdetail/CL05B104KO5NNNC/C1525,2026-11-09,"Basic common MCU, PSRAM and connector high-frequency bypass part.",https://www.lcsc.com/datasheet/C1525.pdf,candidate
C18,1,100n,Capacitor_SMD:C_0402_1005Metric,Samsung Electro-Mechanics,CL05B104KO5NNNC,C1525,Basic,JLCPCB_SMT,https://jlcpcb.com/partdetail/CL05B104KO5NNNC/C1525,2026-11-09,"Basic common MCU, PSRAM and connector high-frequency bypass part.",https://www.lcsc.com/datasheet/C1525.pdf,candidate
C19,1,100n,Capacitor_SMD:C_0402_1005Metric,Samsung Electro-Mechanics,CL05B104KO5NNNC,C1525,Basic,JLCPCB_SMT,https://jlcpcb.com/partdetail/CL05B104KO5NNNC/C1525,2026-11-09,"Basic common MCU, PSRAM and connector high-frequency bypass part.",https://www.lcsc.com/datasheet/C1525.pdf,candidate
C20,1,100n,Capacitor_SMD:C_0402_1005Metric,Samsung Electro-Mechanics,CL05B104KO5NNNC,C1525,Basic,JLCPCB_SMT,https://jlcpcb.com/partdetail/CL05B104KO5NNNC/C1525,2026-11-09,"Basic common MCU, PSRAM and connector high-frequency bypass part.",https://www.lcsc.com/datasheet/C1525.pdf,candidate
C21,1,100n,Capacitor_SMD:C_0402_1005Metric,Samsung Electro-Mechanics,CL05B104KO5NNNC,C1525,Basic,JLCPCB_SMT,https://jlcpcb.com/partdetail/CL05B104KO5NNNC/C1525,2026-11-09,"Basic common MCU, PSRAM and connector high-frequency bypass part.",https://www.lcsc.com/datasheet/C1525.pdf,candidate
C22,1,100n,Capacitor_SMD:C_0402_1005Metric,Samsung Electro-Mechanics,CL05B104KO5NNNC,C1525,Basic,JLCPCB_SMT,https://jlcpcb.com/partdetail/CL05B104KO5NNNC/C1525,2026-11-09,"Basic common MCU, PSRAM and connector high-frequency bypass part.",https://www.lcsc.com/datasheet/C1525.pdf,candidate
D1,1,BAT54X,Diode_SMD:D_SOD-523,R+O,BAT54X,C19627026,Extended,JLCPCB_SMT,https://jlcpcb.com/partdetail/BAT54X/C19627026,2026-11-10,"User-selected Extended SMT R+O BAT54X / C19627026, SOD-523, 30V/200mA. Five identical upper clamps; pad 1 cathode to 3V3, pad 2 anode at the protected MCU node. Retain the accepted sub-mA forward-voltage margin and nominal proxy-model SPICE evidence.",https://datasheet.lcsc.com/datasheet/pdf/cb06a61a226c47be292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,accepted_BAT54_voltage_margin_risk
D2,1,BAT54X,Diode_SMD:D_SOD-523,R+O,BAT54X,C19627026,Extended,JLCPCB_SMT,https://jlcpcb.com/partdetail/BAT54X/C19627026,2026-11-10,"User-selected Extended SMT R+O BAT54X / C19627026, SOD-523, 30V/200mA. Five identical upper clamps; pad 1 cathode to 3V3, pad 2 anode at the protected MCU node. Retain the accepted sub-mA forward-voltage margin and nominal proxy-model SPICE evidence.",https://datasheet.lcsc.com/datasheet/pdf/cb06a61a226c47be292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,accepted_BAT54_voltage_margin_risk
D3,1,BAT54X,Diode_SMD:D_SOD-523,R+O,BAT54X,C19627026,Extended,JLCPCB_SMT,https://jlcpcb.com/partdetail/BAT54X/C19627026,2026-11-10,"User-selected Extended SMT R+O BAT54X / C19627026, SOD-523, 30V/200mA. Five identical upper clamps; pad 1 cathode to 3V3, pad 2 anode at the protected MCU node. Retain the accepted sub-mA forward-voltage margin and nominal proxy-model SPICE evidence.",https://datasheet.lcsc.com/datasheet/pdf/cb06a61a226c47be292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,accepted_BAT54_voltage_margin_risk
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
